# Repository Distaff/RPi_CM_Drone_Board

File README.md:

# Raspberry Pi Compute Module Drone Board (CMDB)

## Description
Used as a lightweight onboard processing unit for AGH Drone Engineering builds. Provides power supply and necessary I/O for Raspberry Pi CM5 module.

IARC HAT Provides programmable ESP32-S3, with SX-1262 for LoRa connectivity, killswitch that disables FC, and ESC/FC connectors.

Weight of both boards is less than 40g.

## PCB Design

### Carrier Board

Layout:

3D render:
| Front                                                        | Back                                                         |
| ------------------------------------------------------------ | ------------------------------------------------------------ |
|    |      |

### IARC HAT

Layout:

3D render:
| Front                                                        | Back                                                         |
| ------------------------------------------------------------ | ------------------------------------------------------------ |
|    |      |

## Authors
- Piotr Kądziela (Schematic, PCB Design)
- Miłosz Ryguła (PCB review)

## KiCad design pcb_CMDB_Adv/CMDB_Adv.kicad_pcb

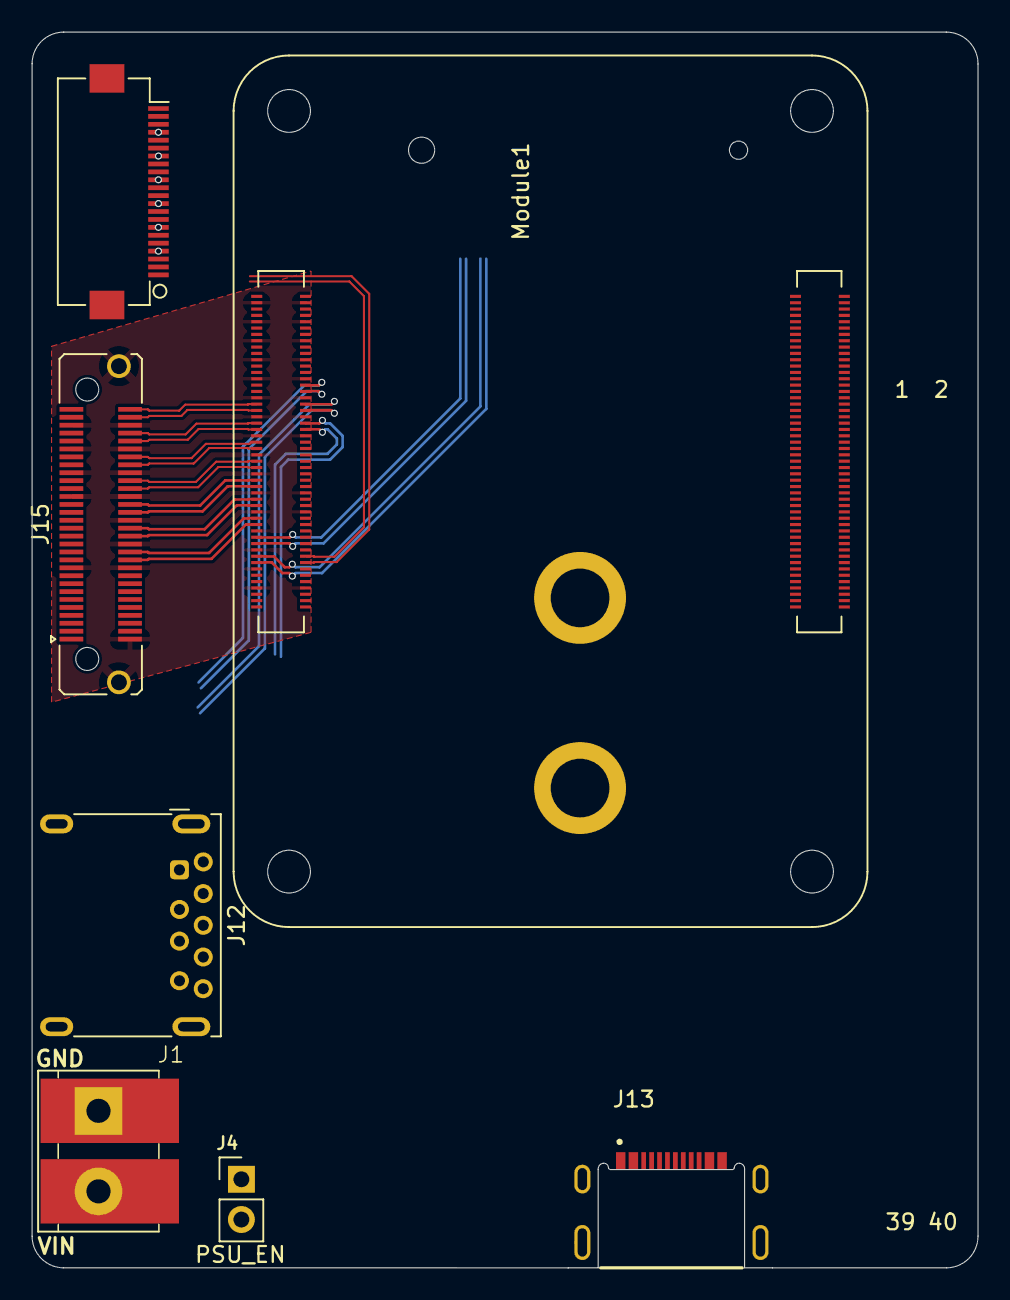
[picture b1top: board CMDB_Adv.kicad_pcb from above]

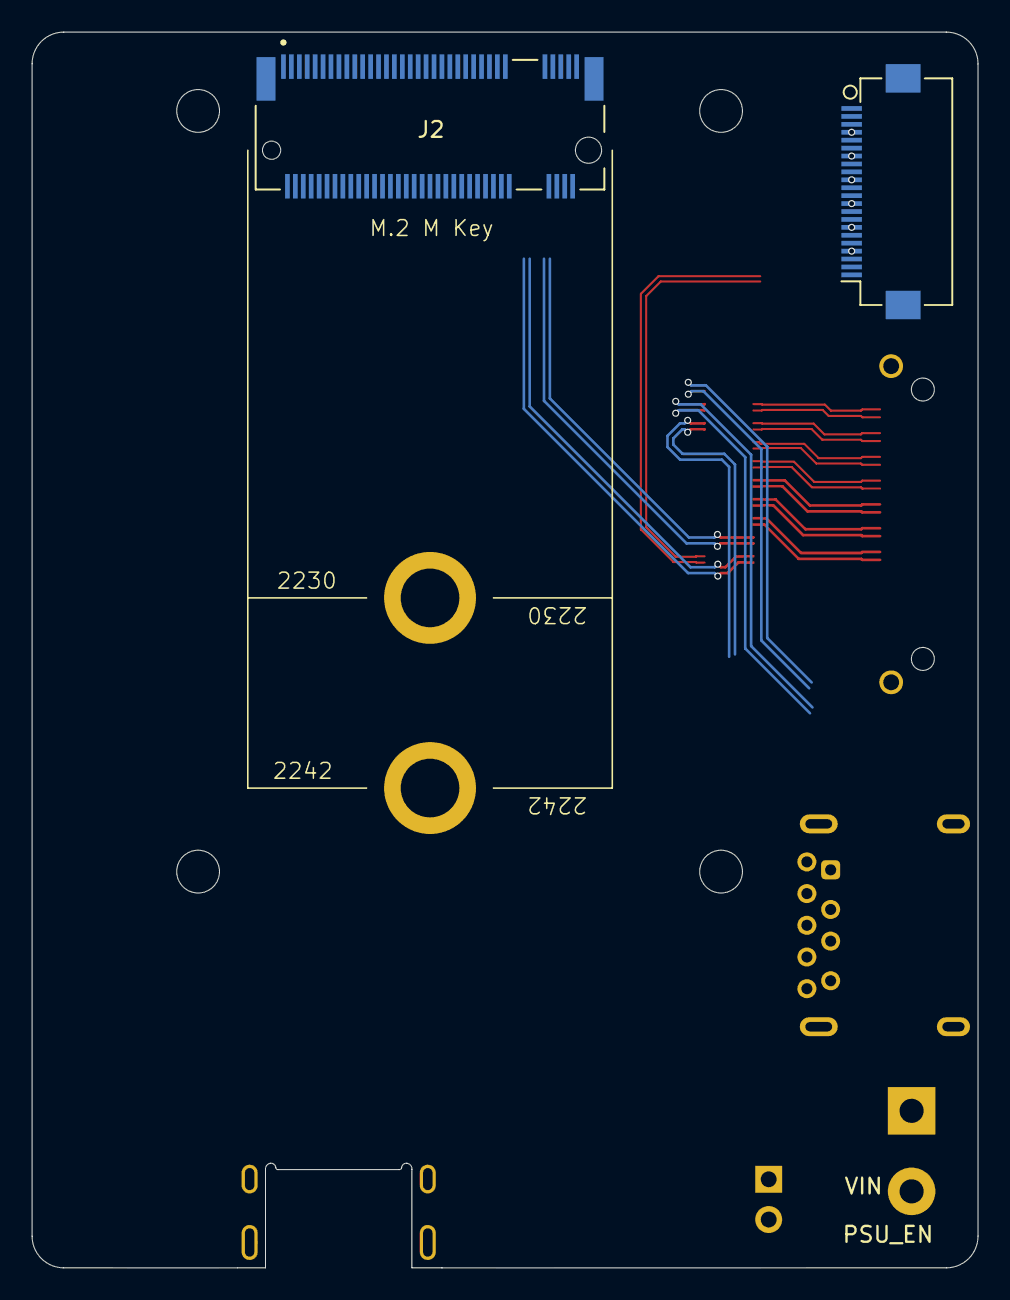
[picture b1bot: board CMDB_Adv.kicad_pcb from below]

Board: 6 copper layers, 59.7 x 78.0 mm, 9 parts (2 on the bottom side), 77 nets.

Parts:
J1: POWER TERMINAL; Power Terminal
J2: Bus_M.2_Socket_M; M.2 M Key socket
J4: J_PSU_EN; PinHeader_1x02_P2.54mm_Vertical
J12: CONN_USB3_A; USB3_A_Molex_48393-001
J13: CONN_USB_PWR_OTG; GCT_USB4510-03-1-A_REVA
J15: CONN_DOCK; Samtec_LSHM-130-xx.x-x-DV-S_2x30-1SH_P0.50mm_Vertical
J16: CONN_CAM1; Hirose_FH12-22S-0.5SH_1x22-1MP_P0.50mm_Horizontal
J17: CONN_CAM0; Hirose_FH12-22S-0.5SH_1x22-1MP_P0.50mm_Horizontal
Module1: ComputeModule5-CM5; Raspberry-Pi-5-Compute-Module

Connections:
/CM5/+3.3v_RPi: Module1.78 (GPIO_VREF(1.8v/3.3v_Input)), Module1.84 (+3.3v_(Output)), Module1.86 (+3.3v_(Output))
/CM5/+5v: Module1.77 (+5v_(Input)), Module1.79 (+5v_(Input)), Module1.81 (+5v_(Input)), Module1.83 (+5v_(Input)), Module1.85 (+5v_(Input)), Module1.87 (+5v_(Input))
/CM5/CAM0_GPIO0: J17.17, Module1.97 (CAM_GPIO0)
/CM5/CAM0_GPIO1: J17.18, Module1.100 (CAM_GPIO1)
/CM5/HDMI0.CEC: J15.15, Module1.151 (HDMI0_CEC)
/CM5/HDMI0.CK_N: J15.59, Module1.190 (HDMI0_CLK_N)
/CM5/HDMI0.CK_P: J15.57, Module1.188 (HDMI0_CLK_P)
/CM5/HDMI0.D0_N: J15.53, Module1.184 (HDMI0_TX0_N)
/CM5/HDMI0.D0_P: J15.51, Module1.182 (HDMI0_TX0_P)
/CM5/HDMI0.D1_N: J15.47, Module1.178 (HDMI0_TX1_N)
/CM5/HDMI0.D1_P: J15.45, Module1.176 (HDMI0_TX1_P)
/CM5/HDMI0.D2_N: J15.41, Module1.172 (HDMI0_TX2_N)
/CM5/HDMI0.D2_P: J15.39, Module1.170 (HDMI0_TX2_P)
/CM5/HDMI0.HP: J15.17, Module1.153 (HDMI0_HOTPLUG)
/CM5/HDMI0.SCL: J15.11, Module1.200 (HDMI0_SCL)
/CM5/HDMI0.SDA: J15.13, Module1.199 (HDMI0_SDA)
/CM5/HDMI1.CEC: J15.16, Module1.149 (HDMI1_CEC)
/CM5/HDMI1.CK_N: J15.60, Module1.166 (HDMI1_CLK_N)
/CM5/HDMI1.CK_P: J15.58, Module1.164 (HDMI1_CLK_P)
/CM5/HDMI1.D0_N: J15.54, Module1.160 (HDMI1_TX0_N)
/CM5/HDMI1.D0_P: J15.52, Module1.158 (HDMI1_TX0_P)
/CM5/HDMI1.D1_N: J15.48, Module1.154 (HDMI1_TX1_N)
/CM5/HDMI1.D1_P: J15.46, Module1.152 (HDMI1_TX1_P)
/CM5/HDMI1.D2_N: J15.42, Module1.148 (HDMI1_TX2_N)
/CM5/HDMI1.D2_P: J15.40, Module1.146 (HDMI1_TX2_P)
/CM5/HDMI1.HP: J15.18, Module1.143 (HDMI1_HOTPLUG)
/CM5/HDMI1.SCL: J15.12, Module1.147 (HDMI1_SCL)
/CM5/HDMI1.SDA: J15.14, Module1.145 (HDMI1_SDA)
/CM5/MIPI0.CK_N: J17.8, Module1.127 (MIPI0_C_N)
/CM5/MIPI0.CK_P: J17.9, Module1.129 (MIPI0_C_P)
/CM5/MIPI0.D0_N: J17.2, Module1.115 (MIPI0_D0_N)
/CM5/MIPI0.D0_P: J17.3, Module1.117 (MIPI0_D0_P)
/CM5/MIPI0.D1_N: J17.5, Module1.121 (MIPI0_D1_N)
/CM5/MIPI0.D1_P: J17.6, Module1.123 (MIPI0_D1_P)
/CM5/MIPI0.D2_N: J17.11, Module1.133 (MIPI0_D2_N)
/CM5/MIPI0.D2_P: J17.12, Module1.135 (MIPI0_D2_P)
/CM5/MIPI0.D3_N: J17.14, Module1.139 (MIPI0_D3_N)
/CM5/MIPI0.D3_P: J17.15, Module1.141 (MIPI0_D3_P)
/CM5/MIPI0_ID_SCL: J17.20, Module1.80 (SCL0)
/CM5/MIPI0_ID_SDA: J17.21, Module1.82 (SDA0)
/CM5/MIPI1.CK_N: J16.8, Module1.187 (MIPI1_C_N)
/CM5/MIPI1.CK_P: J16.9, Module1.189 (MIPI1_C_P)
/CM5/MIPI1.D0_N: J16.2, Module1.175 (MIPI1_D0_N)
/CM5/MIPI1.D0_P: J16.3, Module1.177 (MIPI1_D0_P)
/CM5/MIPI1.D1_N: J16.5, Module1.181 (MIPI1_D1_N)
/CM5/MIPI1.D1_P: J16.6, Module1.183 (MIPI1_D1_P)
/CM5/MIPI1.D2_N: J16.11, Module1.193 (MIPI1_D2_N)
/CM5/MIPI1.D2_P: J16.12, Module1.195 (MIPI1_D2_P)
/CM5/MIPI1.D3_N: J16.14, Module1.194 (MIPI1_D3_N)
/CM5/MIPI1.D3_P: J16.15, Module1.196 (MIPI1_D3_P)
/CM5/PCIe.CLK_N: J2.53 (REFCLKn), Module1.112 (PCIe_CLK_N)
/CM5/PCIe.CLK_P: J2.55 (REFCLKp), Module1.110 (PCIe_CLK_P)
/CM5/PCIe.RX_N: J2.41 (PETn0), Module1.118 (PCIe_RX_N)
/CM5/PCIe.RX_P: J2.43 (PETp0), Module1.116 (PCIe_RX_P)
/CM5/PCIe.TX_N: J2.47 (PERn0), Module1.124 (PCIe_TX_N)
/CM5/PCIe.TX_P: J2.49 (PERp0), Module1.122 (PCIe_TX_P)
/CM5/PCIe.nCLKREQ: J2.52 (~CLKREQ), Module1.102 (PCIe_nCLKREQ)
/CM5/PCIe.nRST: J2.50 (~PERST), Module1.109 (PCIe_nRST)
/CM5/PCIe.nWAKE: J2.54 (~PEWAKE), Module1.104 (PCIE_nWAKE)
/CM5/USB0.D_N: J15.30, Module1.136 (USB3-0-D_N)
/CM5/USB0.D_P: J15.28, Module1.134 (USB3-0-D_P)
/CM5/USB0.RX_N: J15.22, Module1.128 (USB3-0-RX_N)
/CM5/USB0.RX_P: J15.24, Module1.130 (USB3-0-RX_P)
/CM5/USB0.TX_N: J15.34, Module1.140 (USB3-0-TX_N)
/CM5/USB0.TX_P: J15.36, Module1.142 (USB3-0-TX_P)
/CM5/USB1.D_N: J12.6 (SSRX+), Module1.165 (USB3-1-D_N)
/CM5/USB1.D_P: J12.5 (SSRX-), Module1.163 (USB3-1-D_P)
/CM5/USB1.RX_N: J12.2 (D-), Module1.157 (USB3-1-RX_N)
/CM5/USB1.RX_P: J12.3 (D+), Module1.159 (USB3-1-RX_P)
/CM5/USB1.TX_N: J12.8 (SSTX-), Module1.169 (USB3-1-TX_N)
/CM5/USB1.TX_P: J12.9 (SSTX+), Module1.171 (USB3-1-TX_P)
/Connectors/+3.3v: J15.1, J16.22, J17.22
/Connectors/USBC.D_N: J13.A7 (D-), J13.B7 (D-)
/Connectors/USBC.D_P: J13.A6 (D+), J13.B6 (D+)
/M2_3V3: J2.2 (3.3V), J2.4 (3.3V), J2.12 (3.3V), J2.14 (3.3V), J2.16 (3.3V), J2.18 (3.3V), J2.70 (3.3V), J2.72 (3.3V), J2.74 (3.3V)
/PSU/VIN: J1.2 (VIN), J4.1
GND: J1.1 (GND), J2.1 (GND), J2.3 (GND), J2.9 (GND), J2.15 (GND), J2.21 (GND), J2.27 (GND), J2.33 (GND), J2.39 (GND), J2.45 (GND), J2.51 (GND), J2.57 (GND), J2.71 (GND), J2.73 (GND), J2.75 (GND), J2.M1 (GND2230), J2.M2 (GND2242), J2.S1, J2.S2, J12.4 (GND), J12.7 (DRAIN), J12.10 (SHIELD), J13.S1 (SHIELD), J15.2, J15.19, J15.20, J15.26, J15.32, J15.37, J15.38, J15.43, J15.44, J15.49, J15.50, J15.55, J15.56, J15.SH (Shield), J16.1, J16.4, J16.7, J16.10, J16.13, J16.16, J16.19, J17.1, J17.4, J17.7, J17.10, J17.13, J17.16, J17.19, Module1.1 (GND), Module1.2 (GND), Module1.4 (Ethernet_Pair1_P), Module1.6 (Ethernet_Pair1_N), Module1.7 (GND), Module1.8 (GND), Module1.11 (Ethernet_Pair2_P), Module1.13 (GND), Module1.14 (GND), Module1.22 (GND), Module1.23 (GND), Module1.32 (GND), Module1.33 (GND), Module1.35 (ID_SC), Module1.36 (ID_SD), Module1.41 (GPIO25), Module1.42 (GND), Module1.43 (GND), Module1.52 (GND), Module1.53 (GND), Module1.59 (GND), Module1.60 (GND), Module1.62 (SD_CMD), Module1.65 (GND), Module1.66 (GND), Module1.71 (GND), Module1.74 (GND), Module1.98 (GND), Module1.107 (GND), Module1.108 (GND), Module1.113 (GND), Module1.114 (GND), Module1.119 (GND), Module1.120 (GND), Module1.125 (GND), Module1.126 (GND), Module1.131 (GND), Module1.132 (GND), Module1.137 (GND), Module1.138 (GND), Module1.144 (GND), Module1.150 (GND), Module1.155 (GND), Module1.156 (GND), Module1.161 (GND), Module1.162 (GND), Module1.167 (GND), Module1.168 (GND), Module1.173 (GND), Module1.174 (GND), Module1.179 (GND), Module1.180 (GND), Module1.185 (GND), Module1.186 (GND), Module1.191 (GND), Module1.192 (GND), Module1.197 (GND), Module1.198 (GND)

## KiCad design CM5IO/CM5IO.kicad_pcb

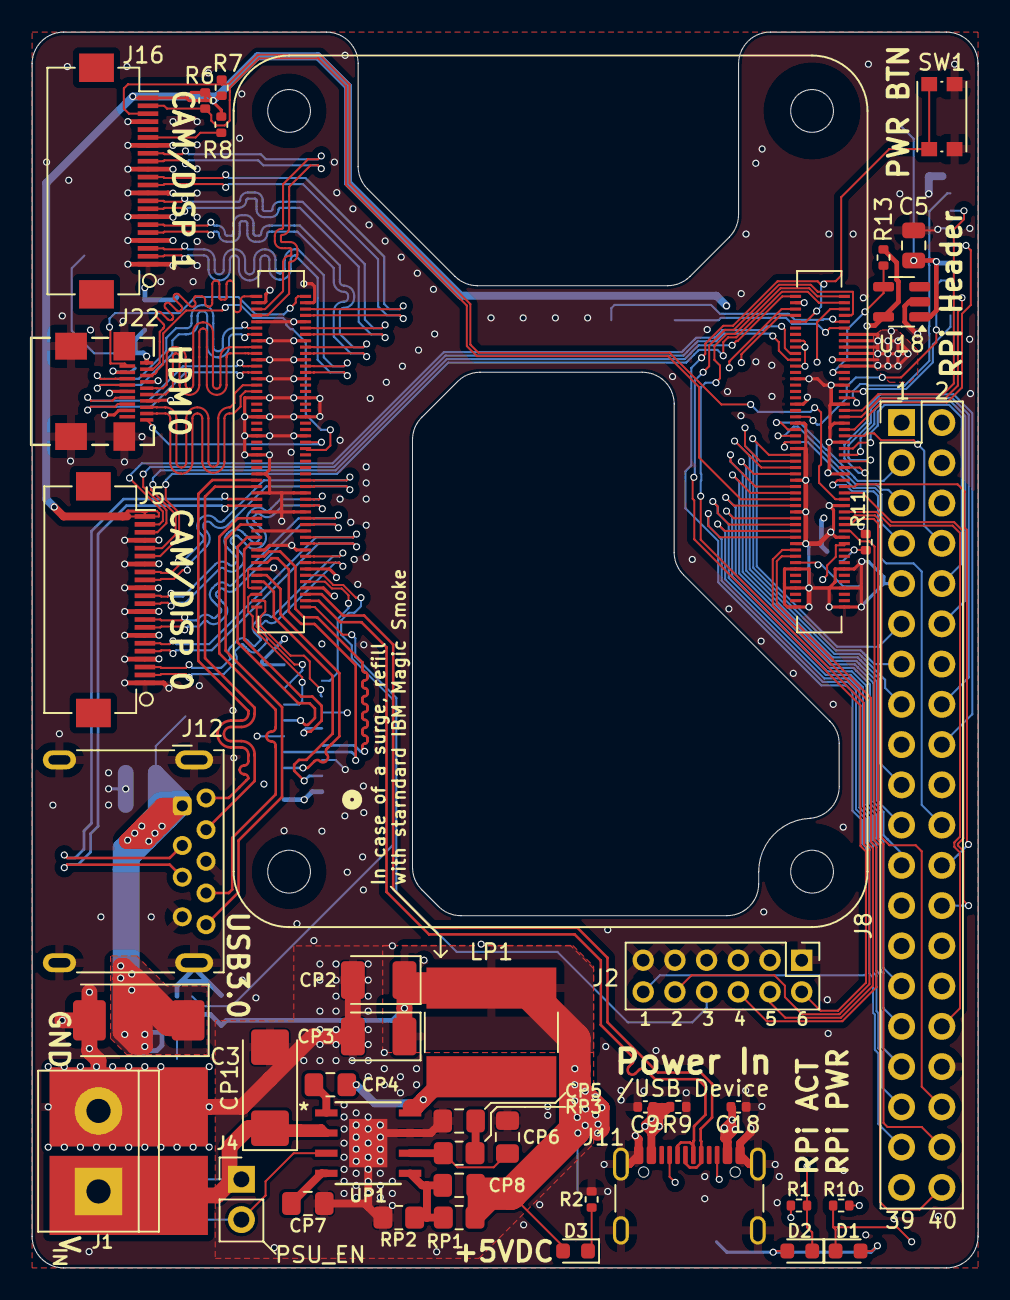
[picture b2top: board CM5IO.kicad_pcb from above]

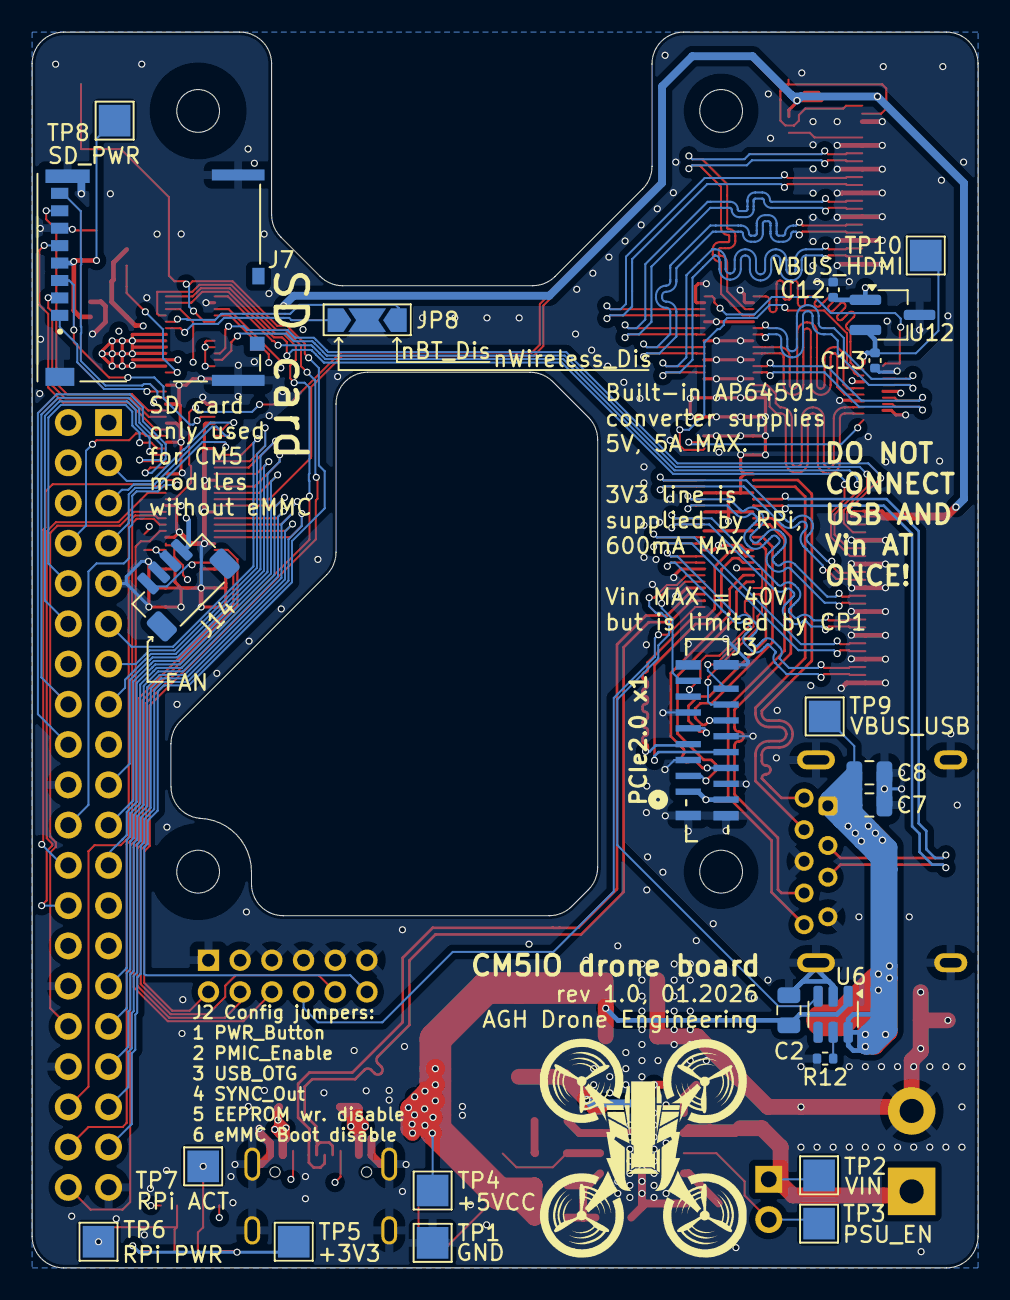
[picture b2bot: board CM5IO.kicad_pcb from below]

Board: 4 copper layers, 59.7 x 78.0 mm, 65 parts (22 on the bottom side), 123 nets.

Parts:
C2, C5, C7, C8: 10u; C_0805_2012Metric
C3: 100uF; CP_EIA-7343-31_Kemet-D
C9, C12, C13, C18: 100n; C_0402_1005Metric
CP1: 10uF; CP_EIA-6032-28_Kemet-C_HandSolder
CP2, CP3: 22uF; CP_EIA-3528-21_Kemet-B_HandSolder
CP4: 100nF; C_0805_2012Metric_Pad1.18x1.45mm_HandSolder
CP5: 2.7nF; C_0805_2012Metric_Pad1.18x1.45mm_HandSolder
CP6: 33pF; C_0805_2012Metric_Pad1.18x1.45mm_HandSolder
CP7: 10nF; C_0805_2012Metric_Pad1.18x1.45mm_HandSolder
CP8: OPEN; C_0805_2012Metric_Pad1.18x1.45mm_HandSolder
D1, D3: LED Red; LED_0603_1608Metric
D2: LED Green; LED_0603_1608Metric
H9: VIN_SOLDERPOINT; SolderWirePad_1x01_SMD_5x10mm
H10: GND_SOLDERPOINT; SolderWirePad_1x01_SMD_5x10mm
J1: POWER TERMINAL; TerminalBlock_bornier-2_P5.08mm
J2: Conn_02x06_Odd_Even; PinHeader_2x06_P2.00mm_Vertical
J3: 62674-161121ALF; CON16_1X16_DUT_58XF_GLE
J4: J_PSU_EN; PinHeader_1x02_P2.54mm_Vertical
J5, J16: Conn_01x22_Female; Hirose_FH12-22S-0.5SH_1x22-1MP_P0.50mm_Horizontal
J7: Micro_SD_Card_Det; SDCARD_MOLEX_503398-1892
J8: THD-20-R; PinHeader_2x20_P2.54mm_Vertical
J11: USB_C_Receptacle_USB2.0; USB_C_Receptacle_GCT_USB4105-xx-A_16P_TopMnt_Horizontal
J12: USB3_A; USB3_A_Molex_48393-001
J14: JST_SHBM04B-SRSS-TB; JST_SH_BM04B-SRSS-TB_1x04-1MP_P1.00mm_Vertical
J22: 46765-1301; CONN_467651301_MOL
JP8: BT_WIFI_DISABLE; SolderJumper-3_P2.0mm_Open_TrianglePad1.0x1.5mm
LP1: 3.6uH; L_Bourns-SRN8040_8x8.15mm
Module1: ComputeModule5-CM5; Raspberry-Pi-5-Compute-Module
R1, R2, R10: 1k; R_0402_1005Metric
R6, R7, R8, R9: 2.2K 1%; R_0402_1005Metric
R11, R13: 10K 1%; R_0402_1005Metric
R12: 15K 1%; R_0402_1005Metric
RP1: 115K; R_0805_2012Metric_Pad1.20x1.40mm_HandSolder
RP2: 22.1K; R_0805_2012Metric_Pad1.20x1.40mm_HandSolder
RP3: 15.8K; R_0805_2012Metric_Pad1.20x1.40mm_HandSolder
SW1: Right angle Tact button; SW_Push_1P1T_NO_CK_KMR2
TP1: TP GND; TestPoint_Pad_2.0x2.0mm
TP2: TP VIN; TestPoint_Pad_2.0x2.0mm
TP3: TP PSU_EN; TestPoint_Pad_2.0x2.0mm
TP4: TP +5VCC; TestPoint_Pad_2.0x2.0mm
TP5: TP +3V3; TestPoint_Pad_2.0x2.0mm
TP6: TP nPWR; TestPoint_Pad_2.0x2.0mm
TP7: TP nACT; TestPoint_Pad_2.0x2.0mm
TP8: TP SD_PWR; TestPoint_Pad_2.0x2.0mm
TP9: TP VBUS_USB; TestPoint_Pad_2.0x2.0mm
TP10: TP VBUS_HDMI; TestPoint_Pad_2.0x2.0mm
U6: AP22653W6; SOT-23-6
U12: RT9742SNGV; TSOT-23_HandSoldering
U18: RT9742GGJ5; SOT-23-5
UP1: AP64501SP-13; SOP_AP64501SP-13_DIO

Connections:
/+3.3v: D1.2 (A), D2.2 (A), J5.22, J8.1, J8.17, J16.22, Module1.78 (GPIO_VREF(1.8v/3.3v_Input)), Module1.84 (+3.3v_(Output)), Module1.86 (+3.3v_(Output)), R6.1, R7.1, R8.1, R11.1, R13.1, TP5.1, U18.5 (IN)
/+5v: C2.1, C9.1, C12.1, C18.1, CP2.1, CP3.1, CP8.1, D3.2 (A), J3.1, J3.2, J8.2, J8.4, J11.A4 (VBUS), J11.A9 (VBUS), J11.B4 (VBUS), J11.B9 (VBUS), J14.1, LP1.2, Module1.77 (+5v_(Input)), Module1.79 (+5v_(Input)), Module1.81 (+5v_(Input)), Module1.83 (+5v_(Input)), Module1.85 (+5v_(Input)), Module1.87 (+5v_(Input)), R9.1, RP1.1, TP4.1, U6.1 (IN), U12.1 (IN)
/CC1: J11.A5 (CC1), Module1.94 (CC1)
/CC2: J11.B5 (CC2), Module1.96 (CC2)
/CM5_GPIO ( Ethernet, GPIO, SDCARD)/BT_nDis: JP8.3 (B), Module1.91 (BT_nDisable)
/CM5_GPIO ( Ethernet, GPIO, SDCARD)/CAM_GPIO0: J5.17, Module1.97 (CAM_GPIO0)
/CM5_GPIO ( Ethernet, GPIO, SDCARD)/CAM_GPIO1: J5.18, Module1.100 (CAM_GPIO1)
/CM5_GPIO ( Ethernet, GPIO, SDCARD)/EEPROM_nWP: J2.4, Module1.20 (EEPROM_nWP)
/CM5_GPIO ( Ethernet, GPIO, SDCARD)/GPIO2: J8.3, Module1.58 (GPIO2)
/CM5_GPIO ( Ethernet, GPIO, SDCARD)/GPIO3: J8.5, Module1.56 (GPIO3)
/CM5_GPIO ( Ethernet, GPIO, SDCARD)/GPIO4: J8.7, Module1.54 (GPIO4)
/CM5_GPIO ( Ethernet, GPIO, SDCARD)/GPIO5: J8.29, Module1.34 (GPIO5)
/CM5_GPIO ( Ethernet, GPIO, SDCARD)/GPIO6: J8.31, Module1.30 (GPIO6)
/CM5_GPIO ( Ethernet, GPIO, SDCARD)/GPIO7: J8.26, Module1.37 (GPIO7)
/CM5_GPIO ( Ethernet, GPIO, SDCARD)/GPIO8: J8.24, Module1.39 (GPIO8)
/CM5_GPIO ( Ethernet, GPIO, SDCARD)/GPIO9: J8.21, Module1.40 (GPIO9)
/CM5_GPIO ( Ethernet, GPIO, SDCARD)/GPIO10: J8.19, Module1.44 (GPIO10)
/CM5_GPIO ( Ethernet, GPIO, SDCARD)/GPIO11: J8.23, Module1.38 (GPIO11)
/CM5_GPIO ( Ethernet, GPIO, SDCARD)/GPIO12: J8.32, Module1.31 (GPIO12)
/CM5_GPIO ( Ethernet, GPIO, SDCARD)/GPIO13: J8.33, Module1.28 (GPIO13)
/CM5_GPIO ( Ethernet, GPIO, SDCARD)/GPIO14: J8.8, Module1.55 (GPIO14)
/CM5_GPIO ( Ethernet, GPIO, SDCARD)/GPIO15: J8.10, Module1.51 (GPIO15)
/CM5_GPIO ( Ethernet, GPIO, SDCARD)/GPIO16: J8.36, Module1.29 (GPIO16)
/CM5_GPIO ( Ethernet, GPIO, SDCARD)/GPIO17: J8.11, Module1.50 (GPIO17)
/CM5_GPIO ( Ethernet, GPIO, SDCARD)/GPIO18: J8.12, Module1.49 (GPIO18)
/CM5_GPIO ( Ethernet, GPIO, SDCARD)/GPIO19: J8.35, Module1.26 (GPIO19)
/CM5_GPIO ( Ethernet, GPIO, SDCARD)/GPIO20: J8.38, Module1.27 (GPIO20)
/CM5_GPIO ( Ethernet, GPIO, SDCARD)/GPIO21: J8.40, Module1.25 (GPIO21)
/CM5_GPIO ( Ethernet, GPIO, SDCARD)/GPIO22: J8.15, Module1.46 (GPIO22)
/CM5_GPIO ( Ethernet, GPIO, SDCARD)/GPIO23: J8.16, Module1.47 (GPIO23)
/CM5_GPIO ( Ethernet, GPIO, SDCARD)/GPIO24: J8.18, Module1.45 (GPIO24)
/CM5_GPIO ( Ethernet, GPIO, SDCARD)/GPIO25: J8.22, Module1.41 (GPIO25)
/CM5_GPIO ( Ethernet, GPIO, SDCARD)/GPIO26: J8.37, Module1.24 (GPIO26)
/CM5_GPIO ( Ethernet, GPIO, SDCARD)/GPIO27: J8.13, Module1.48 (GPIO27)
/CM5_GPIO ( Ethernet, GPIO, SDCARD)/PMIC_ENABLE: J2.10, Module1.99 (PMIC_ENABLE)
/CM5_GPIO ( Ethernet, GPIO, SDCARD)/PWM: J14.2, Module1.19 (FAN_PWM), R11.2
/CM5_GPIO ( Ethernet, GPIO, SDCARD)/PWR_BUT: J2.12, Module1.92 (PWR_BUT), SW1.1
/CM5_GPIO ( Ethernet, GPIO, SDCARD)/SD_CLK: J7.5 (CLK), Module1.57 (SD_CLK)
/CM5_GPIO ( Ethernet, GPIO, SDCARD)/SD_CMD: J7.3 (CMD), Module1.62 (SD_CMD)
/CM5_GPIO ( Ethernet, GPIO, SDCARD)/SD_DAT0: J7.7 (DAT0), Module1.63 (SD_DAT0)
/CM5_GPIO ( Ethernet, GPIO, SDCARD)/SD_DAT1: J7.8 (DAT1), Module1.67 (SD_DAT1)
/CM5_GPIO ( Ethernet, GPIO, SDCARD)/SD_DAT2: J7.1 (DAT2), Module1.69 (SD_DAT2)
/CM5_GPIO ( Ethernet, GPIO, SDCARD)/SD_DAT3: J7.2 (DAT3/CD), Module1.61 (SD_DAT3)
/CM5_GPIO ( Ethernet, GPIO, SDCARD)/SD_PWR: C5.1, J7.4 (VDD), TP8.1, U18.1 (OUT)
/CM5_GPIO ( Ethernet, GPIO, SDCARD)/SD_PWR_ON: Module1.75 (SD_PWR_ON), R13.2, U18.4 (EN)
/CM5_GPIO ( Ethernet, GPIO, SDCARD)/SYNC_OUT: J2.6, Module1.18 (Ethernet_SYNC_OUT(3.3v))
/CM5_GPIO ( Ethernet, GPIO, SDCARD)/TACHO: J14.4, Module1.16 (FAN_TACHO)
/CM5_GPIO ( Ethernet, GPIO, SDCARD)/USBOTG: J2.8, Module1.101 (USB_OTG_ID)
/CM5_GPIO ( Ethernet, GPIO, SDCARD)/WL_nDis: JP8.1 (A), Module1.89 (WiFi_nDisable)
/CM5_GPIO ( Ethernet, GPIO, SDCARD)/nPWR_LED: Module1.95 (LED_nPWR), R10.2
/CM5_GPIO ( Ethernet, GPIO, SDCARD)/nRPIBOOT: J2.2, Module1.93 (nRPIBOOT)
/CM5_HighSpeed/DPHY0_C_N: J5.8, Module1.127 (MIPI0_C_N)
/CM5_HighSpeed/DPHY0_C_P: J5.9, Module1.129 (MIPI0_C_P)
/CM5_HighSpeed/DPHY0_D0_N: J5.2, Module1.115 (MIPI0_D0_N)
/CM5_HighSpeed/DPHY0_D0_P: J5.3, Module1.117 (MIPI0_D0_P)
/CM5_HighSpeed/DPHY0_D1_N: J5.5, Module1.121 (MIPI0_D1_N)
/CM5_HighSpeed/DPHY0_D1_P: J5.6, Module1.123 (MIPI0_D1_P)
/CM5_HighSpeed/DPHY0_D2_N: J5.11, Module1.133 (MIPI0_D2_N)
/CM5_HighSpeed/DPHY0_D2_P: J5.12, Module1.135 (MIPI0_D2_P)
/CM5_HighSpeed/DPHY0_D3_N: J5.14, Module1.139 (MIPI0_D3_N)
/CM5_HighSpeed/DPHY0_D3_P: J5.15, Module1.141 (MIPI0_D3_P)
/CM5_HighSpeed/DPHY1_C_N: J16.8, Module1.187 (MIPI1_C_N)
/CM5_HighSpeed/DPHY1_C_P: J16.9, Module1.189 (MIPI1_C_P)
/CM5_HighSpeed/DPHY1_D0_N: J16.2, Module1.175 (MIPI1_D0_N)
/CM5_HighSpeed/DPHY1_D0_P: J16.3, Module1.177 (MIPI1_D0_P)
/CM5_HighSpeed/DPHY1_D1_N: J16.5, Module1.181 (MIPI1_D1_N)
/CM5_HighSpeed/DPHY1_D1_P: J16.6, Module1.183 (MIPI1_D1_P)
/CM5_HighSpeed/DPHY1_D2_N: J16.11, Module1.193 (MIPI1_D2_N)
/CM5_HighSpeed/DPHY1_D2_P: J16.12, Module1.195 (MIPI1_D2_P)
/CM5_HighSpeed/DPHY1_D3_N: J16.14, Module1.194 (MIPI1_D3_N)
/CM5_HighSpeed/DPHY1_D3_P: J16.15, Module1.196 (MIPI1_D3_P)
/CM5_HighSpeed/HDMI0_CEC: J22.15 (CEC), Module1.151 (HDMI0_CEC)
/CM5_HighSpeed/HDMI0_CK_N: J22.14 (CK-), Module1.190 (HDMI0_CLK_N)
/CM5_HighSpeed/HDMI0_CK_P: J22.12 (CK+), Module1.188 (HDMI0_CLK_P)
/CM5_HighSpeed/HDMI0_D0_N: J22.11 (D0-), Module1.184 (HDMI0_TX0_N)
/CM5_HighSpeed/HDMI0_D0_P: J22.9 (D0+), Module1.182 (HDMI0_TX0_P)
/CM5_HighSpeed/HDMI0_D1_N: J22.8 (D1-), Module1.178 (HDMI0_TX1_N)
/CM5_HighSpeed/HDMI0_D1_P: J22.6 (D1+), Module1.176 (HDMI0_TX1_P)
/CM5_HighSpeed/HDMI0_D2_N: J22.5 (D2-), Module1.172 (HDMI0_TX2_N)
/CM5_HighSpeed/HDMI0_D2_P: J22.3 (D2+), Module1.170 (HDMI0_TX2_P)
/CM5_HighSpeed/HDMI0_HOTPLUG: J22.1 (HPD/HEAC-), Module1.153 (HDMI0_HOTPLUG)
/CM5_HighSpeed/HDMI0_SCL: J22.17 (SCL), Module1.200 (HDMI0_SCL)
/CM5_HighSpeed/HDMI0_SDA: J22.18 (SDA), Module1.199 (HDMI0_SDA)
/CM5_HighSpeed/HDMI_5v: C13.1, J22.19 (+5V), TP10.1, U12.2 (OUT)
/CM5_HighSpeed/PCIE_CLKREQ_N: J3.15, Module1.102 (PCIe_nCLKREQ)
/CM5_HighSpeed/PCIE_CLK_N: J3.5, Module1.112 (PCIe_CLK_N)
/CM5_HighSpeed/PCIE_CLK_P: J3.4, Module1.110 (PCIe_CLK_P)
/CM5_HighSpeed/PCIE_DET_WAKE: J3.14, Module1.104 (PCIE_nWAKE)
/CM5_HighSpeed/PCIE_PWR_EN: J3.13, Module1.106 (PCIE_PWR_EN)
/CM5_HighSpeed/PCIE_RST_B: J3.16, Module1.109 (PCIe_nRST)
/CM5_HighSpeed/PCIE_RX_N: J3.8, Module1.118 (PCIe_RX_N)
/CM5_HighSpeed/PCIE_RX_P: J3.7, Module1.116 (PCIe_RX_P)
/CM5_HighSpeed/PCIE_TX_N: J3.11, Module1.124 (PCIe_TX_N)
/CM5_HighSpeed/PCIE_TX_P: J3.10, Module1.122 (PCIe_TX_P)
/CM5_HighSpeed/SCL0: J5.20, Module1.80 (SCL0)
/CM5_HighSpeed/SCL1: J16.20, Module1.35 (ID_SC), R7.2
/CM5_HighSpeed/SDA0: J5.21, Module1.82 (SDA0)
/CM5_HighSpeed/SDA1: J16.21, Module1.36 (ID_SD), R6.2
/CM5_HighSpeed/USB3-0-D_N: J12.2 (D-), Module1.136 (USB3-0-D_N)
/CM5_HighSpeed/USB3-0-D_P: J12.3 (D+), Module1.134 (USB3-0-D_P)
/CM5_HighSpeed/USB3-0-RX_N: J12.5 (SSRX-), Module1.128 (USB3-0-RX_N)
/CM5_HighSpeed/USB3-0-RX_P: J12.6 (SSRX+), Module1.130 (USB3-0-RX_P)
/CM5_HighSpeed/USB3-0-TX_N: J12.8 (SSTX-), Module1.140 (USB3-0-TX_N)
/CM5_HighSpeed/USB3-0-TX_P: J12.9 (SSTX+), Module1.142 (USB3-0-TX_P)
/CM5_HighSpeed/VBUS: C3.1, C7.1, C8.1, J12.1 (VBUS), TP9.1, U6.6 (OUT)
/CM5_HighSpeed/VBUS_EN: Module1.111 (VBUS_EN), U6.3 (EN)
/PSU/PSU_EN: J4.2, TP3.1, UP1.3 (EN)
/PSU/SW: CP4.2, LP1.1, UP1.8 (SW)
/USB2_N: J11.A7 (D-), J11.B7 (D-), Module1.103 (USB2_N)
/USB2_P: J11.A6 (D+), J11.B6 (D+), Module1.105 (USB2_P)
/VIN: CP1.1, H9.1 (MP), J1.1, J4.1, TP2.1, UP1.2 (VIN)
GND: C2.2, C3.2, C5.2, C7.2, C8.2, C9.2, C12.2, C13.2, C18.2, CP1.2, CP2.2, CP3.2, CP5.2, CP6.2, CP7.1, H10.1 (MP), J1.2, J2.1, J2.3, J2.5, J2.7, J2.9, J2.11, J3.3, J3.6, J3.9, J3.12, J3.SH1, J3.SH2, J3.SH3, J3.SH4, J5.1, J5.4, J5.7, J5.10, J5.13, J5.16, J5.19, J7.6 (VSS), J7.11 (SHIELD), J8.6, J8.9, J8.14, J8.20, J8.25, J8.30, J8.34, J8.39, J11.A1 (GND), J11.A12 (GND), J11.B1 (GND), J11.B12 (GND), J11.S1 (SHIELD), J12.4 (GND), J12.7 (DRAIN), J12.10 (SHIELD), J14.3, J16.1, J16.4, J16.7, J16.10, J16.13, J16.16, J16.19, J22.4 (D2S), J22.7 (D1S), J22.10 (D0S), J22.13 (CKS), J22.16 (GND), J22.SH, JP8.2 (C), Module1.1 (GND), Module1.2 (GND), Module1.7 (GND), Module1.8 (GND), Module1.13 (GND), Module1.14 (GND), Module1.22 (GND), Module1.23 (GND), Module1.32 (GND), Module1.33 (GND), Module1.42 (GND), Module1.43 (GND), Module1.52 (GND), Module1.53 (GND), Module1.59 (GND), Module1.60 (GND), Module1.65 (GND), Module1.66 (GND), Module1.71 (GND), Module1.74 (GND), Module1.98 (GND), Module1.107 (GND), Module1.108 (GND), Module1.113 (GND), Module1.114 (GND), Module1.119 (GND), Module1.120 (GND), Module1.125 (GND), Module1.126 (GND), Module1.131 (GND), Module1.132 (GND), Module1.137 (GND), Module1.138 (GND), Module1.144 (GND), Module1.150 (GND), Module1.155 (GND), Module1.156 (GND), Module1.161 (GND), Module1.162 (GND), Module1.167 (GND), Module1.168 (GND), Module1.173 (GND), Module1.174 (GND), Module1.179 (GND), Module1.180 (GND), Module1.185 (GND), Module1.186 (GND), Module1.191 (GND), Module1.192 (GND), Module1.197 (GND), Module1.198 (GND), R2.2, R9.2, R12.2, RP2.2, SW1.2, TP1.1, U6.2 (GND), U12.3 (GND), U18.2 (GND), UP1.7 (GND), UP1.9 (EP)
unnamed: CP5.1, RP3.2
unnamed: D1.1 (K), R10.1, TP6.1
unnamed: D2.1 (K), R1.1, TP7.1
unnamed: D3.1 (K), R2.1
unnamed: J16.17, R8.2
unnamed: Module1.21 (LED_nACT), R1.2
unnamed: R12.1, U6.5 (ILIM)
unnamed: CP4.1, UP1.1 (BST)
unnamed: CP6.1, RP3.1, UP1.6 (COMP)
unnamed: CP8.2, RP1.2, RP2.1, UP1.5 (FB)
unnamed: CP7.2, UP1.4 (SS)

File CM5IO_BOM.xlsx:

Qty/ board | Ref | Value | Footprint | Desc | Part No. | MOUSER |  | Farnell |  | TME
 |  |  |  |  |  | Unit Price | Code | Unit Price | Code | Unit Price | Code | min. Il. na 10 płytek
4 | C9,C12,C13,C18 | 100n | Capacitor_SMD:C_0402_1005Metric | 0.1uF 10% 16V Ceramic Capacitor X7R 0402 (1005 Metric) | - |  |  |  |  | 3.9190000000000003E-2 | 04025C104KAT2A | 12 | 0.47028000000000003
1 | CP6 | 33pF | Capacitor_SMD:C_0805_2012Metric_Pad1.18x1.45mm_HandSolder | - | - |  |  |  |  | 0.20480000000000001 | 08055A330KAT2A | 12 | 2.4576000000000002
1 | CP5 | 2.7nF | Capacitor_SMD:C_0805_2012Metric_Pad1.18x1.45mm_HandSolder | - | - |  |  |  |  | 0.18210000000000001 | 08055C272KAT2A | 12 | 2.1852
1 | CP7 | 10nF | Capacitor_SMD:C_0805_2012Metric_Pad1.18x1.45mm_HandSolder | - | - |  |  |  |  | 0.1421 | 08055C103KAT2A | 12 | 1.7052
1 | CP4 | 100nF | Capacitor_SMD:C_0805_2012Metric_Pad1.18x1.45mm_HandSolder | - | - |  |  |  |  | 4.1669999999999999E-2 | 08055C104KAT2A | 12 | 0.50004000000000004
4 | C2,C5,C7,C8 | 10u | Capacitor_SMD:C_0805_2012Metric | 10uF 10% 10V Ceramic Capacitor X7R 0805 (2012 Metric) | - |  |  |  |  | 0.28220000000000001 | 08055C105KAT2A | 42 | 11.852399999999999
3 | R1,R2,R10 | 1k | Resistor_SMD:R_0402_1005Metric | Resistor 1K M1005 1% 63mW | - |  |  |  |  | 3.3119999999999997E-2 | SMD0402-1K-1% | 100 | 3.3119999999999998
4 | R6,R7,R8,R9 | 2.2K 1% | Resistor_SMD:R_0402_1005Metric | Resistor 2.2K M1005 1% 63mW | - |  |  |  |  | 3.9050000000000001E-2 | SMD0402-2K2-1% | 100 | 3.9050000000000002
2 | R11,R13 | 10K 1% | Resistor_SMD:R_0402_1005Metric | Resistor 10K M1005 1% 63mW | - |  |  |  |  | 1.7569999999999999E-2 | SMD0402-10K-1% | 100 | 1.7569999999999999
1 | R12 | 15K 1% | Resistor_SMD:R_0402_1005Metric | Resistor 15K M1005 1% 63mW | - |  |  |  |  | 3.6560000000000002E-2 | SMD0402-15K-1% | 100 | 3.6560000000000001
1 | RP1 | 115K | Resistor_SMD:R_0805_2012Metric_Pad1.20x1.40mm_HandSolder | - | - |  |  |  |  | 0.21560000000000001 | ERA6AEB1153V | 12 | 2.5872000000000002
1 | RP2 | 22.1K | Resistor_SMD:R_0805_2012Metric_Pad1.20x1.40mm_HandSolder | - | - |  |  |  |  | 5.9389999999999998E-2 | SMD0805-22K1-1% | 100 | 5.9390000000000001
1 | RP3 | 15.8K | Resistor_SMD:R_0805_2012Metric_Pad1.20x1.40mm_HandSolder | - | - |  |  |  |  | 6.7129999999999995E-2 | SMD0805-15.8K-1% | 100 | 6.7129999999999992
1 | J1 | POWER TERMINAL | TerminalBlock:TerminalBlock_bornier-2_P5.08mm | - | - |  |  |  |  |  | Will be unused |  | 0
1 | J2 | Conn_02x06_Odd_Even | Connector_PinHeader_2.00mm:PinHeader_2x06_P2.00mm_Vertical | PinHeader_2x06_P2.54mm_Vertical | - |  |  |  |  | 1.093 | ZL303-2X40P | 10 | 10.93
2 | J2 |  |  | Zwory do J2 |  |  |  |  |  | 0.29389999999999999 | JUMPER-2.0/B | 12 | 3.5267999999999997
1 | J4 | J_PSU_EN | Connector_PinHeader_2.54mm:PinHeader_1x02_P2.54mm_Vertical | - | - |  |  |  |  |  |  |  | 0
1 | J8 | THD-20-R | Connector_PinHeader_2.54mm:PinHeader_2x20_P2.54mm_Vertical | PinHeader_2x20_P2.54mm_Vertical | THD-20-R
 |  |  |  |  |  |  |  |  |  |  |  | SUMA | 61.496720000000003
1 | CP1 | 10uF | Capacitor_Tantalum_SMD:CP_EIA-3528-21_Kemet-C_HandSolder | Tantalum, Kemet-C, 10uF@35V min. | - |  |  |  |  | 3.7360000000000002 | TAJC106K035R
2 | CP2,CP3 | 22uF | Capacitor_Tantalum_SMD:CP_EIA-3528-21_Kemet-B_HandSolder | Tantalum, Kemet-B, 22uF@10V min. | - |  |  |  |  | 1.643 | TAJB226K016R
1 | C3 | 100uF | Capacitor_Tantalum_SMD:CP_EIA-7343-31_Kemet-D | Kemet-D, 10V | - |  |  |  |  | 2.2789999999999999 | TAJD106K035R
2 | D1,D3 | LED Red | LED_SMD:LED_0603_1608Metric | Red 620nm LED Indication - Discrete 2.2V 2-SMD, No Lead | SML-A12U8TT86Q | 0.38300000000000001 | 859-LTST-S270KRKT | 1.65 | 3434715 | 0 | -
1 | D2 | LED Green | LED_SMD:LED_0603_1608Metric | Green 572nm LED Indication - Discrete 2.2V 2-SMD, No Lead | SML-A12M8TT86N | 0.30499999999999999 | 859-LTST-S270KGKT | 1.64 | 3434712 | 0 | -
2 | J5,J16 | Conn_01x22_Female | CM5IO:Hirose_FH12-22S-0.5SH_1x22-1MP_P0.50mm_Horizontal | 22 Position FFC, FPC Connector Contacts, Bottom 0.020" (0.50mm) Surface Mount, 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 | FH12-22S-0.5SH55 | 5.68 | 798-FH12-22S-0.5SH55 | 7.17 | 2300373 | 0 | -
1 | J7 | Micro_SD_Card_Det | CM5IO:SDCARD_MOLEX_503398-1892 | 9 (8 + 1) Position Card Connector microSDâ„¢ Surface Mount, Right Angle Gold | 503398-1892 |  |  |  |  | 8.41 | MX-503398-1892 | Not necessary, if no SD card is used
1 | J11 | USB_C_Receptacle_USB2.0 | Connector_USB:USB_C_Receptacle_GCT_USB4105-xx-A_16P_TopMnt_Horizontal | USBC USB2 data and power connector | USBF31-0171 |  |  |  |  | 2.5059999999999998 | USB4105-GF-A-060 (substitute)
1 | J12 | USB3_A | Connector_USB:USB3_A_Molex_48393-001 | USB 3.0 A connector | 48393-0003 |  |  |  |  | 9.67 | MX-48393-0003
1 | J14 | JST_SHBM04B-SRSS-TB | Connector_JST:JST_SH_BM04B-SRSS-TB_1x04-1MP_P1.00mm_Vertical | 4 pin vertical 1mm pitch connector | SHBM04B-SRSS-TB |  |  |  |  | 1.4419999999999999 | SM04B-SRSS-TB
1 | J22 | 46765-1301 | CM5IO:CONN_467651301_MOL | 0.40mm Pitch Micro HDMI Connector, Right-Angle Receptacle, Surface Mount, with 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 | 46765-1301 | 7.7 | 538-46765-1301 | 8.82 | 2614867 | 0 | -
1 | LP1 | 3.6uH | Inductor_SMD:L_Bourns-SRN8040_8x8.15mm | - | SRN8040HA-3R6M | 1.7 | 652-SRN8040HA-3R6M | 2.52 | 4216300 | 0 | -
2 | Module1 | ComputeModule5-CM5 | CM5IO:Raspberry-Pi-5-Compute-Module | 100 Position Connector Receptacle, Center Strip Contacts Surface Mount Gold | 10164227-1001A1RLF | 5.5529999999999999 | DF40C-100DS-0.4V(51) (substitute) | 7.43 | 4137104 | 0 | -
1 | SW1 | Right angle Tact button | Button_Switch_SMD:SW_Push_1P1T_NO_CK_KMR2 | - | KMR221G LFS |  |  |  |  | 1.0469999999999999 | KMR221GLFS
1 | U6 | AP22653W6 | Package_TO_SOT_SMD:SOT-23-6 | Power Switch/Driver 1:1 P-Channel 2.1A SOT-23-6 | AP22653W6 |  |  |  |  | 1.45 | AP22653W6-7
1 | U12 | RT9742SNGV | Package_TO_SOT_SMD:TSOT-23_HandSoldering | Power Switch/Driver 1:1 N-Channel 500mA SOT-23-3 | RT9742SNGV | 1.04 | 835-RT9742SNGV | 1.5 | 2575555 | 0 | -
1 | U18 | RT9742GGJ5 | Package_TO_SOT_SMD:SOT-23-5 | Power Switch/Driver 1:1 N-Channel 1A TSOT-23-5 | RT9742GGJ5 | 1.19 | 835-RT9742GGJ5 | 0 | - | 0 | - | Not necessary, if no SD card is used
1 | UP1 | AP64501SP-13 | CM5IO:SOP_AP64501SP-13_DIO | - | AP64501SP-13 |  |  |  |  | 7.11 | AP64501SP-13
 |  |  |  |  |  | 35.166999999999994 | SUMA / płytka | 46.980000000000004 | SUMA / płytka | 40.936 | SUMA / płytka

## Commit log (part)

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2026-01-29 change LEDs orientation
2026-02-01 Upload final gerbers with personal touch TM
2026-02-11 update BOM
2026-04-29 Add README for Raspberry Pi Compute Module Drone Board
    Added detailed description and images for the Raspberry Pi Compute Module Drone Board.
